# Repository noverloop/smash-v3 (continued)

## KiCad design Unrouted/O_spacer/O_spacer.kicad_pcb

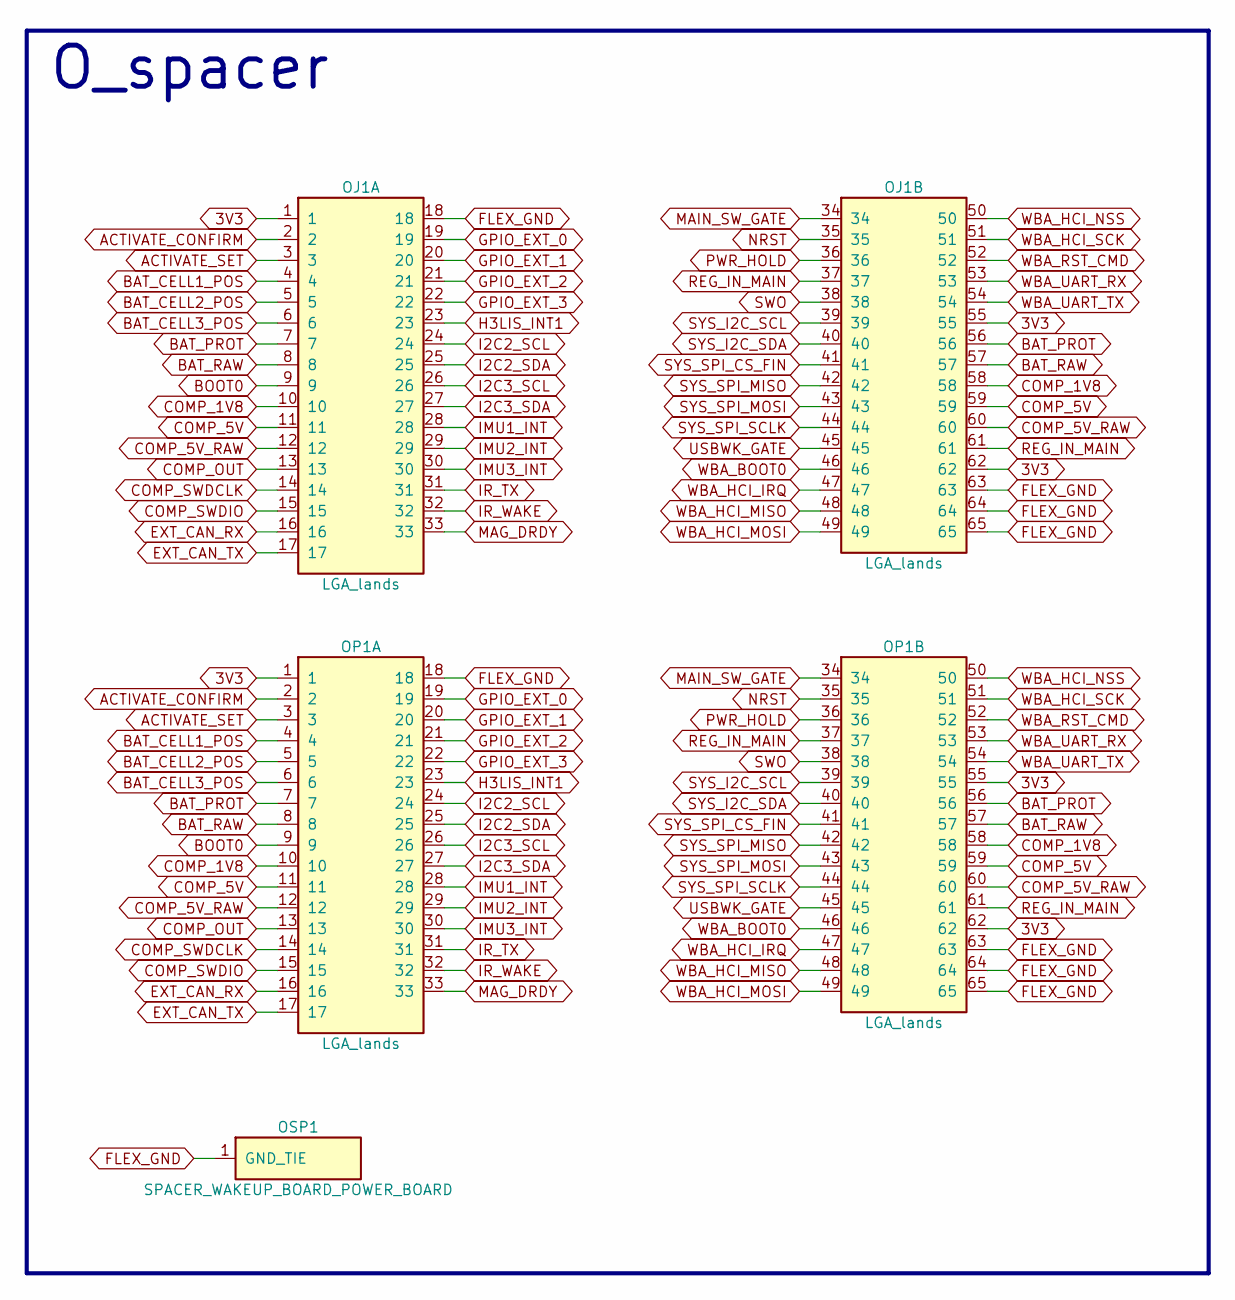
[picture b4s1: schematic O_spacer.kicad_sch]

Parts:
OJ1: LGA_lands; J_spacer_wakeup_board_power_board_top; MPN LGA_lands
OP1: LGA_lands; P_spacer_wakeup_board_power_board_bot; MPN LGA_lands
OSP1: SPACER_WAKEUP_BOARD_POWER_BOARD; Spacer_Mechanical_34mm

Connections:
3V3: OJ1.1, OJ1.55, OJ1.62, OP1.1, OP1.55, OP1.62
ACTIVATE_CONFIRM: OJ1.2, OP1.2
ACTIVATE_SET: OJ1.3, OP1.3
BAT_CELL1_POS: OJ1.4, OP1.4
BAT_CELL2_POS: OJ1.5, OP1.5
BAT_CELL3_POS: OJ1.6, OP1.6
BAT_PROT: OJ1.7, OJ1.56, OP1.7, OP1.56
BAT_RAW: OJ1.8, OJ1.57, OP1.8, OP1.57
BOOT0: OJ1.9, OP1.9
COMP_1V8: OJ1.10, OJ1.58, OP1.10, OP1.58
COMP_5V: OJ1.11, OJ1.59, OP1.11, OP1.59
COMP_5V_RAW: OJ1.12, OJ1.60, OP1.12, OP1.60
COMP_OUT: OJ1.13, OP1.13
COMP_SWDCLK: OJ1.14, OP1.14
COMP_SWDIO: OJ1.15, OP1.15
EXT_CAN_RX: OJ1.16, OP1.16
EXT_CAN_TX: OJ1.17, OP1.17
FLEX_GND: OJ1.18, OJ1.63, OJ1.64, OJ1.65, OP1.18, OP1.63, OP1.64, OP1.65, OSP1.1
GPIO_EXT_0: OJ1.19, OP1.19
GPIO_EXT_1: OJ1.20, OP1.20
GPIO_EXT_2: OJ1.21, OP1.21
GPIO_EXT_3: OJ1.22, OP1.22
H3LIS_INT1: OJ1.23, OP1.23
I2C2_SCL: OJ1.24, OP1.24
I2C2_SDA: OJ1.25, OP1.25
I2C3_SCL: OJ1.26, OP1.26
I2C3_SDA: OJ1.27, OP1.27
IMU1_INT: OJ1.28, OP1.28
IMU2_INT: OJ1.29, OP1.29
IMU3_INT: OJ1.30, OP1.30
IR_TX: OJ1.31, OP1.31
IR_WAKE: OJ1.32, OP1.32
MAG_DRDY: OJ1.33, OP1.33
MAIN_SW_GATE: OJ1.34, OP1.34
NRST: OJ1.35, OP1.35
PWR_HOLD: OJ1.36, OP1.36
REG_IN_MAIN: OJ1.37, OJ1.61, OP1.37, OP1.61
SWO: OJ1.38, OP1.38
SYS_I2C_SCL: OJ1.39, OP1.39
SYS_I2C_SDA: OJ1.40, OP1.40
SYS_SPI_CS_FIN: OJ1.41, OP1.41
SYS_SPI_MISO: OJ1.42, OP1.42
SYS_SPI_MOSI: OJ1.43, OP1.43
SYS_SPI_SCLK: OJ1.44, OP1.44
USBWK_GATE: OJ1.45, OP1.45
WBA_BOOT0: OJ1.46, OP1.46
WBA_HCI_IRQ: OJ1.47, OP1.47
WBA_HCI_MISO: OJ1.48, OP1.48
WBA_HCI_MOSI: OJ1.49, OP1.49
WBA_HCI_NSS: OJ1.50, OP1.50
WBA_HCI_SCK: OJ1.51, OP1.51
WBA_RST_CMD: OJ1.52, OP1.52
WBA_UART_RX: OJ1.53, OP1.53
WBA_UART_TX: OJ1.54, OP1.54

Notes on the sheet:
O_spacer

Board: 2 copper layers, 5 parts (1 on the bottom side), 54 nets, no tracks yet.

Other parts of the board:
OMH1, OMH2: smash_mech_potting

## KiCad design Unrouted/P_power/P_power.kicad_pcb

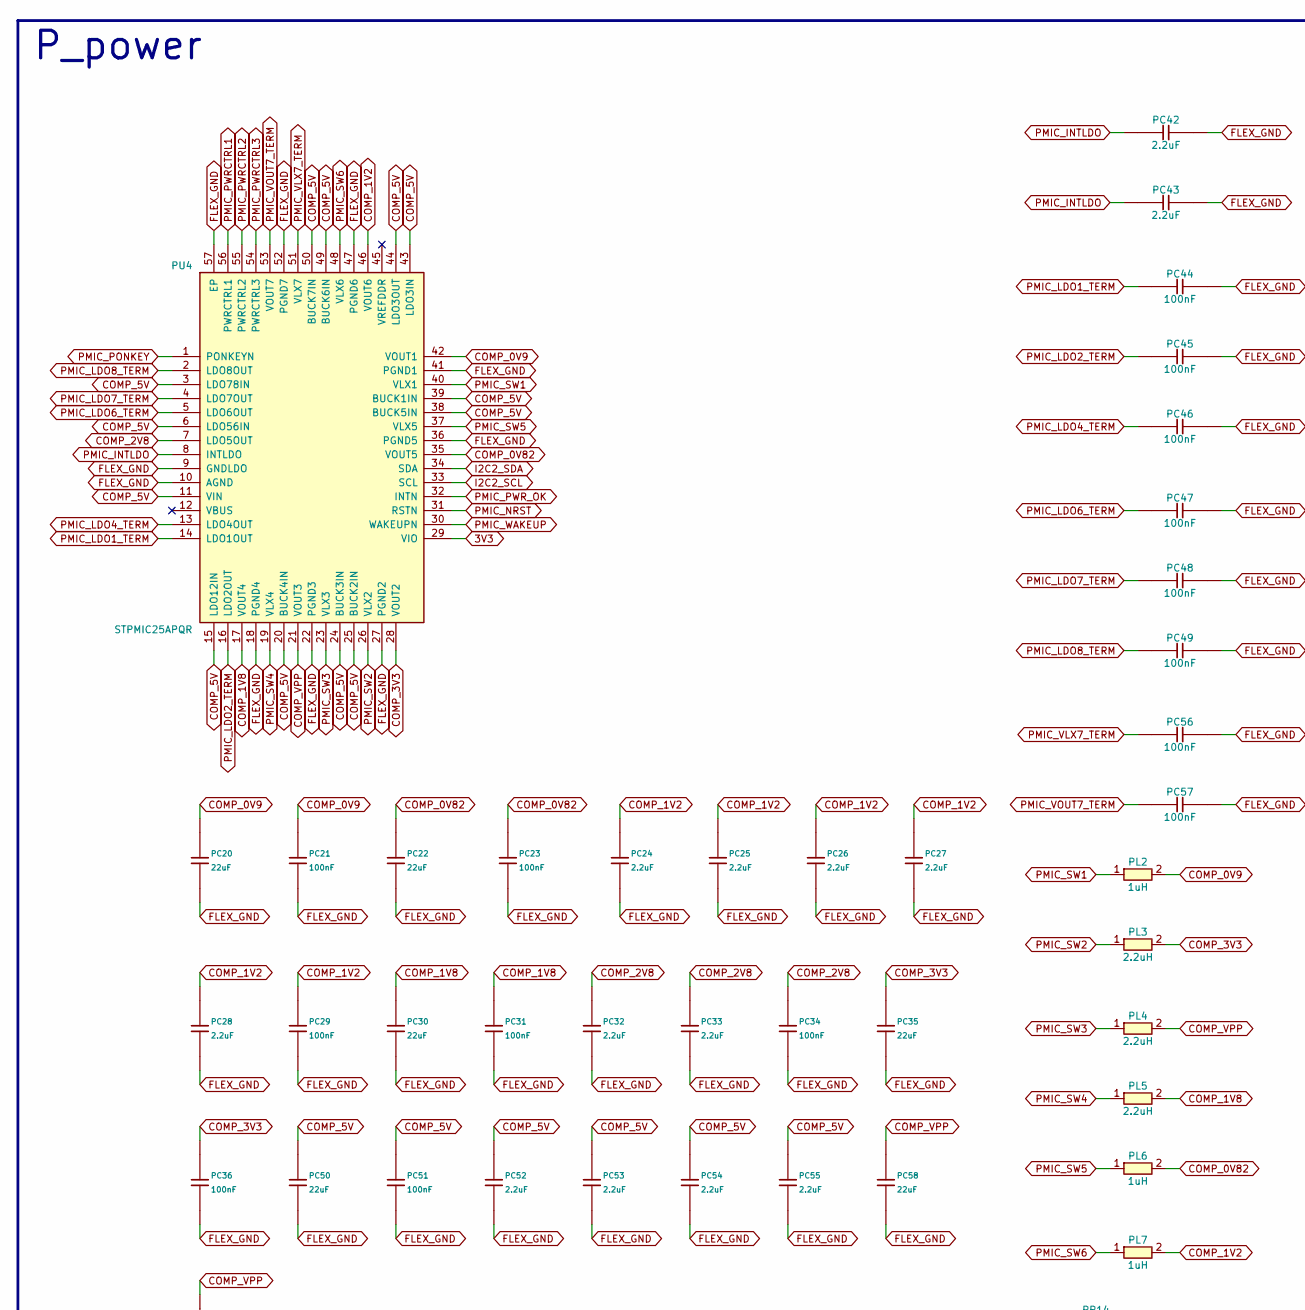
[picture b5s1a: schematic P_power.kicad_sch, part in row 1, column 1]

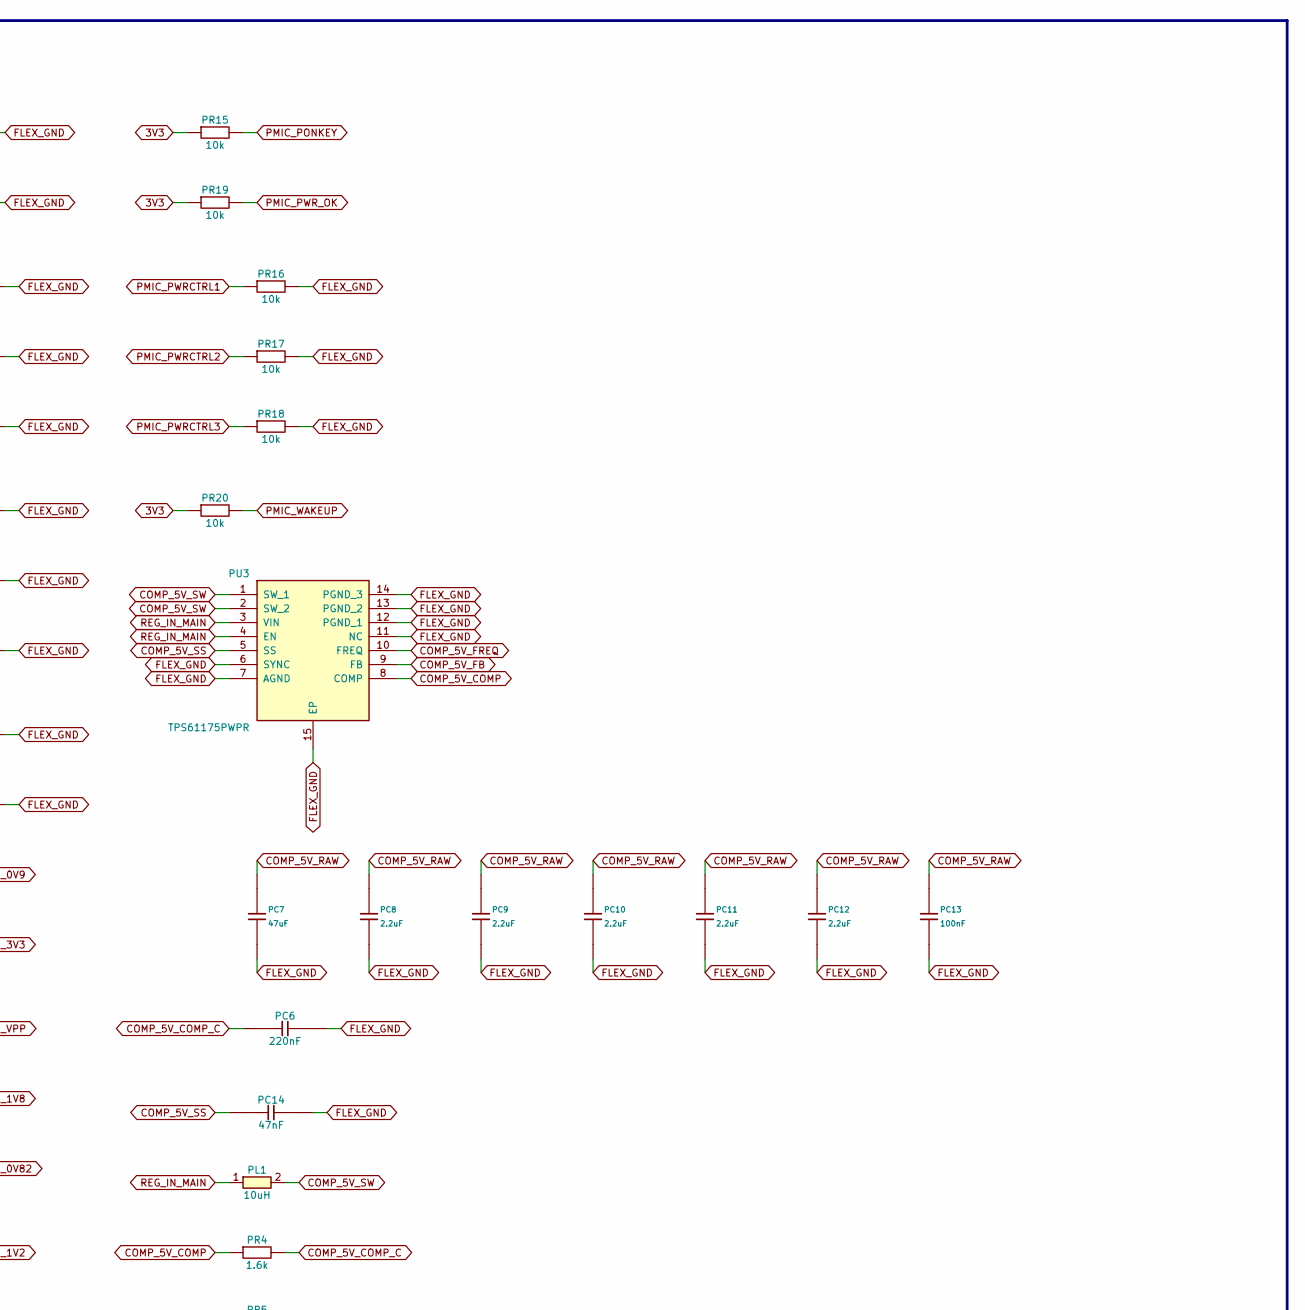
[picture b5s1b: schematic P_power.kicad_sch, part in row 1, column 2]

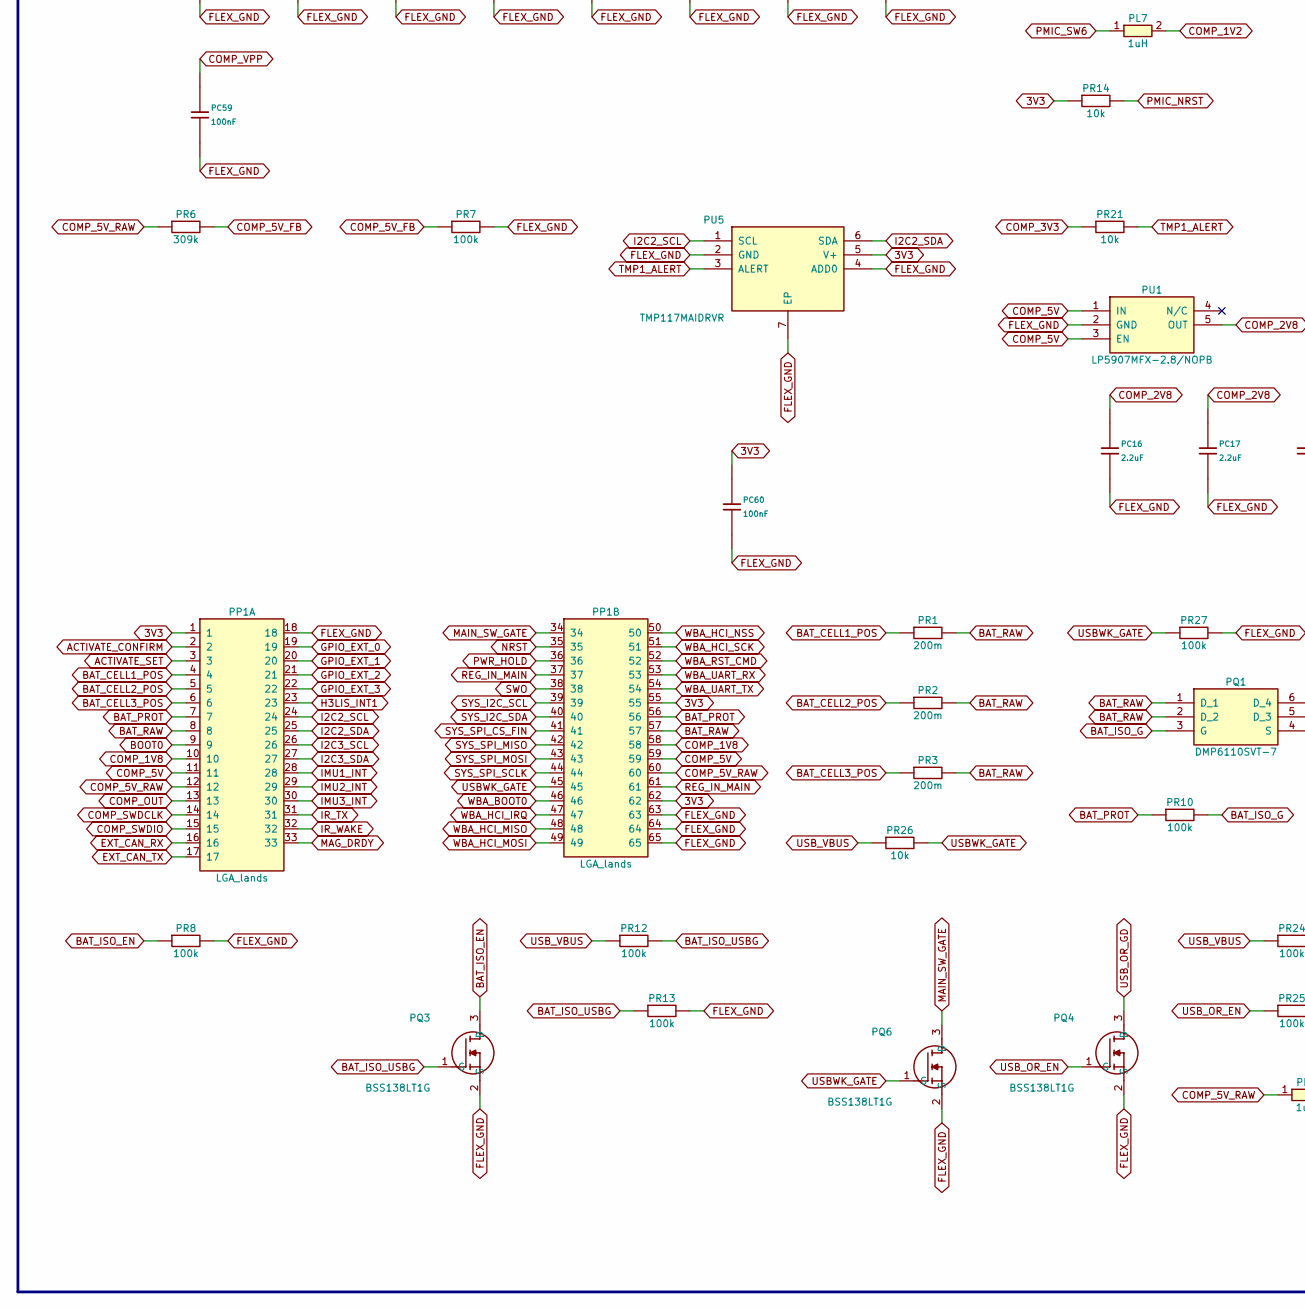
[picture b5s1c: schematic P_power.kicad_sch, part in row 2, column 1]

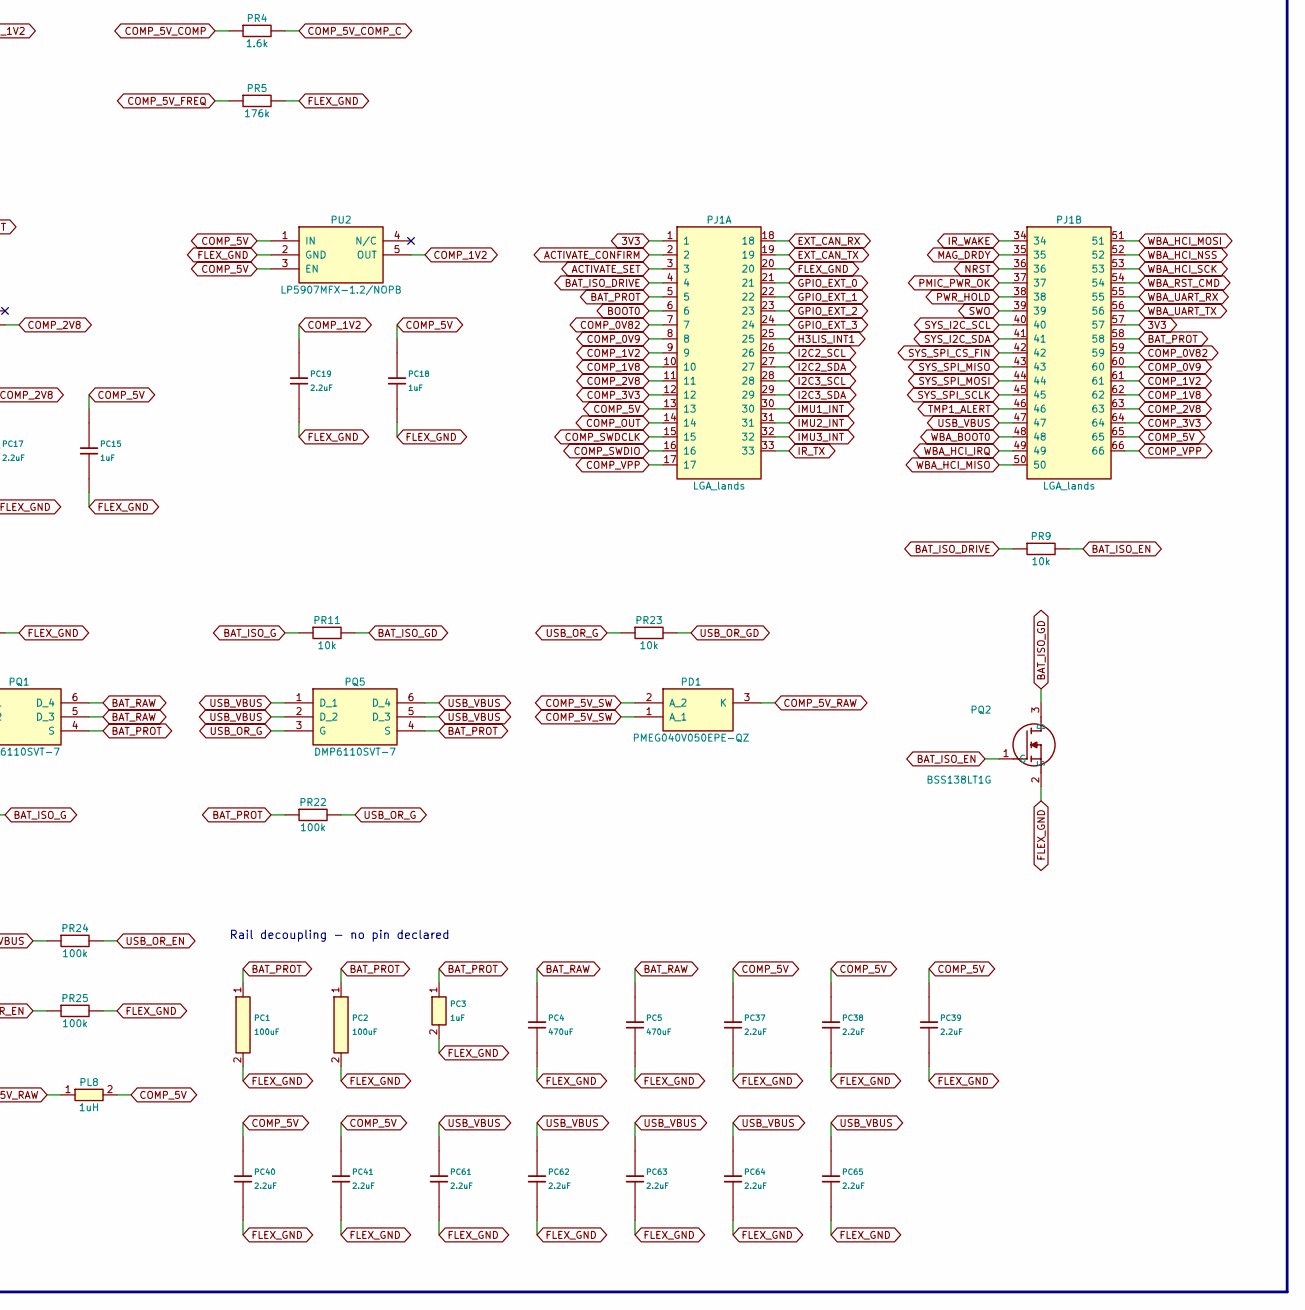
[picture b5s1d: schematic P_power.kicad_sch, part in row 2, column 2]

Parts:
PC1, PC2: 100uF; Capacitor_Tantalum_SMD_CP_EIA-7343-15_Kemet-W; MPN T528W 100uF (7343-15 thinnest variant)
PC3, PC15, PC18: 1uF; Capacitor_SMD_C_0805_2012Metric; MPN C-Series MIL-PRF-32535 X7R 0805 1uF
PC4, PC5: 470uF; Capacitor_Tantalum_SMD_CP_EIA-7343-15_Kemet-W; MPN T528W 470uF (7343-15 thinnest variant)
PC6: 220nF; Capacitor_SMD_C_0603_1608Metric; MPN C-Series MIL-PRF-32535 X7R 0603 220nF
PC7: 47uF; Capacitor_Tantalum_SMD_CP_EIA-7343-15_Kemet-W; MPN T528W 47uF (7343-15 thinnest variant)
PC8, PC9, PC10, PC11, PC12, PC16, PC17, PC19, PC24, PC25, PC26, PC27, PC28, PC32, PC33, PC37, PC38, PC39, PC40, PC41, PC42, PC43, PC52, PC53, PC54, PC55, PC61, PC62, PC63, PC64, PC65: 2.2uF; Capacitor_SMD_C_0603_1608Metric; MPN C-Series MIL-PRF-32535 X7R 0603 2.2uF
PC13, PC21, PC23, PC29, PC31, PC34, PC36, PC44, PC45, PC46, PC47, PC48, PC49, PC51, PC56, PC57, PC59, PC60: 100nF; Capacitor_SMD_C_0402_1005Metric; MPN C0402 X7R 100nF
PC14: 47nF; Capacitor_SMD_C_0402_1005Metric; MPN C0402 X7R 47nF
PC20, PC22, PC30, PC35, PC50, PC58: 22uF; Capacitor_Tantalum_SMD_CP_EIA-3528-12_Kemet-T; MPN T491T 22uF (3528-12 thinnest variant)
PD1: PMEG040V050EPE-QZ; PMEG040V050EPEQZ; MPN PMEG040V050EPE-QZ
PJ1: LGA_lands; J_power_board_spacer_power_board_companion_compute; MPN LGA_lands
PL1: 10uH; INDPM4848X280N; MPN 744043100
PL2, PL6, PL7, PL8: 1uH; Inductor_SMD_L_2012_2.0x1.25mm; MPN TMS201210ALM-1R0MTAA
PL3, PL4, PL5: 2.2uH; Inductor_SMD_L_2012_2.0x1.25mm; MPN TMS201210ALM-2R2MTAA
PP1: LGA_lands; P_power_board_spacer_wakeup_board_power_board; MPN LGA_lands
PQ1, PQ5: DMP6110SVT-7; SOT95P280X100-6N; MPN DMP6110SVT-7
PQ2, PQ3, PQ4, PQ6: BSS138LT1G; SOT96P237X111-3N; MPN BSS138LT1G
PR1, PR2, PR3: 200m; Resistor_SMD_R_0402_1005Metric; MPN CRCW0402 200m 1% e3
PR4: 1.6k; Resistor_SMD_R_0402_1005Metric; MPN CRCW0402 1.6k 1% e3
PR5: 176k; Resistor_SMD_R_0402_1005Metric; MPN CRCW0402 176k 1% e3
PR6: 309k; Resistor_SMD_R_0402_1005Metric; MPN CRCW0402 309k 1% e3
PR7, PR8, PR10, PR12, PR13, PR22, PR24, PR25, PR27: 100k; Resistor_SMD_R_0402_1005Metric; MPN CRCW0402 100k 1% e3
PR9, PR11, PR14, PR15, PR16, PR17, PR18, PR19, PR20, PR21, PR23, PR26: 10k; Resistor_SMD_R_0402_1005Metric; MPN CRCW0402 10k 1% e3
PU1: LP5907MFX-2.8/NOPB; SOT95P280X145-5N; MPN LP5907MFX-2.8/NOPB
PU2: LP5907MFX-1.2/NOPB; SOT95P280X145-5N; MPN LP5907MFX-1.2/NOPB
PU3: TPS61175PWPR; SOP65P640X120-15N; MPN TPS61175PWPR
PU4: STPMIC25APQR; QFN40P650X650X90-57N-D; MPN STPMIC25APQR
PU5: TMP117MAIDRVR; SON65P200X200X80-7N; MPN TMP117MAIDRVR

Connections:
3V3: PC60.1 (+), PJ1.1, PJ1.57, PP1.1, PP1.55, PP1.62, PR14.1, PR15.1, PR19.1, PR20.1, PU4.29 (VIO), PU5.5 (V+)
ACTIVATE_CONFIRM: PJ1.2, PP1.2
ACTIVATE_SET: PJ1.3, PP1.3
BAT_CELL1_POS: PP1.4, PR1.1
BAT_CELL2_POS: PP1.5, PR2.1
BAT_CELL3_POS: PP1.6, PR3.1
BAT_ISO_DRIVE: PJ1.4, PR9.1
BAT_ISO_EN: PQ2.1 (G), PQ3.3 (D), PR8.1, PR9.2
BAT_ISO_G: PQ1.3 (G), PR10.2, PR11.1
BAT_ISO_GD: PQ2.3 (D), PR11.2
BAT_ISO_USBG: PQ3.1 (G), PR12.2, PR13.1
BAT_PROT: PC1.1 (+), PC2.1 (+), PC3.1, PJ1.5, PJ1.58, PP1.7, PP1.56, PQ1.4 (S), PQ5.4 (S), PR10.1, PR22.1
BAT_RAW: PC4.1 (+), PC5.1 (+), PP1.8, PP1.57, PQ1.1 (D_1), PQ1.2 (D_2), PQ1.5 (D_3), PQ1.6 (D_4), PR1.2, PR2.2, PR3.2
BOOT0: PJ1.6, PP1.9
COMP_0V9: PC20.1 (+), PC21.1 (+), PJ1.8, PJ1.60, PL2.2, PU4.42 (VOUT1)
COMP_0V82: PC22.1 (+), PC23.1 (+), PJ1.7, PJ1.59, PL6.2, PU4.35 (VOUT5)
COMP_1V2: PC19.1 (+), PC24.1 (+), PC25.1 (+), PC26.1 (+), PC27.1 (+), PC28.1 (+), PC29.1 (+), PJ1.9, PJ1.61, PL7.2, PU2.5 (OUT), PU4.46 (VOUT6)
COMP_1V8: PC30.1 (+), PC31.1 (+), PJ1.10, PJ1.62, PL5.2, PP1.10, PP1.58, PU4.17 (VOUT4)
COMP_2V8: PC16.1 (+), PC17.1 (+), PC32.1 (+), PC33.1 (+), PC34.1 (+), PJ1.11, PJ1.63, PU1.5 (OUT), PU4.7 (LDO5OUT)
COMP_3V3: PC35.1 (+), PC36.1 (+), PJ1.12, PJ1.64, PL3.2, PR21.1, PU4.28 (VOUT2)
COMP_5V: PC15.1 (+), PC18.1 (+), PC37.1 (+), PC38.1 (+), PC39.1 (+), PC40.1 (+), PC41.1 (+), PC50.1 (+), PC51.1 (+), PC52.1 (+), PC53.1 (+), PC54.1 (+), PC55.1 (+), PJ1.13, PJ1.65, PL8.2, PP1.11, PP1.59, PU1.1 (IN), PU1.3 (EN), PU2.1 (IN), PU2.3 (EN), PU4.3 (LDO78IN), PU4.6 (LDO56IN), PU4.11 (VIN), PU4.15 (LDO12IN), PU4.20 (BUCK4IN), PU4.24 (BUCK3IN), PU4.25 (BUCK2IN), PU4.38 (BUCK5IN), PU4.39 (BUCK1IN), PU4.43 (LDO3IN), PU4.44 (LDO3OUT), PU4.49 (BUCK6IN), PU4.50 (BUCK7IN)
COMP_5V_COMP: PR4.1, PU3.8 (COMP)
COMP_5V_COMP_C: PC6.1 (+), PR4.2
COMP_5V_FB: PR6.2, PR7.1, PU3.9 (FB)
COMP_5V_FREQ: PR5.1, PU3.10 (FREQ)
COMP_5V_RAW: PC7.1 (+), PC8.1 (+), PC9.1 (+), PC10.1 (+), PC11.1 (+), PC12.1 (+), PC13.1 (+), PD1.3 (K), PL8.1, PP1.12, PP1.60, PR6.1
COMP_5V_SS: PC14.1 (+), PU3.5 (SS)
COMP_5V_SW: PD1.1 (A_1), PD1.2 (A_2), PL1.2, PU3.1 (SW_1), PU3.2 (SW_2)
COMP_OUT: PJ1.14, PP1.13
COMP_SWDCLK: PJ1.15, PP1.14
COMP_SWDIO: PJ1.16, PP1.15
COMP_VPP: PC58.1 (+), PC59.1 (+), PJ1.17, PJ1.66, PL4.2, PU4.21 (VOUT3)
EXT_CAN_RX: PJ1.18, PP1.16
EXT_CAN_TX: PJ1.19, PP1.17
FLEX_GND: PC1.2 (-), PC2.2 (-), PC3.2, PC4.2 (-), PC5.2 (-), PC6.2 (-), PC7.2 (-), PC8.2 (-), PC9.2 (-), PC10.2 (-), PC11.2 (-), PC12.2 (-), PC13.2 (-), PC14.2 (-), PC15.2 (-), PC16.2 (-), PC17.2 (-), PC18.2 (-), PC19.2 (-), PC20.2 (-), PC21.2 (-), PC22.2 (-), PC23.2 (-), PC24.2 (-), PC25.2 (-), PC26.2 (-), PC27.2 (-), PC28.2 (-), PC29.2 (-), PC30.2 (-), PC31.2 (-), PC32.2 (-), PC33.2 (-), PC34.2 (-), PC35.2 (-), PC36.2 (-), PC37.2 (-), PC38.2 (-), PC39.2 (-), PC40.2 (-), PC41.2 (-), PC42.2 (-), PC43.2 (-), PC44.2 (-), PC45.2 (-), PC46.2 (-), PC47.2 (-), PC48.2 (-), PC49.2 (-), PC50.2 (-), PC51.2 (-), PC52.2 (-), PC53.2 (-), PC54.2 (-), PC55.2 (-), PC56.2 (-), PC57.2 (-), PC58.2 (-), PC59.2 (-), PC60.2 (-), PC61.2 (-), PC62.2 (-), PC63.2 (-), PC64.2 (-), PC65.2 (-), PJ1.20, PP1.18, PP1.63, PP1.64, PP1.65, PQ2.2 (S), PQ3.2 (S), PQ4.2 (S), PQ6.2 (S), PR5.2, PR7.2, PR8.2, PR13.2, PR16.2, PR17.2, PR18.2, PR25.2, PR27.2, PU1.2 (GND), PU2.2 (GND), PU3.6 (SYNC), PU3.7 (AGND), PU3.11 (NC), PU3.12 (PGND_1), PU3.13 (PGND_2), PU3.14 (PGND_3), PU3.15 (EP), PU4.9 (GNDLDO), PU4.10 (AGND), PU4.18 (PGND4), PU4.22 (PGND3), PU4.27 (PGND2), PU4.36 (PGND5), PU4.41 (PGND1), PU4.47 (PGND6), PU4.52 (PGND7), PU4.57 (EP), PU5.2 (GND), PU5.4 (ADD0), PU5.7 (EP)
GPIO_EXT_0: PJ1.21, PP1.19
GPIO_EXT_1: PJ1.22, PP1.20
GPIO_EXT_2: PJ1.23, PP1.21
GPIO_EXT_3: PJ1.24, PP1.22
H3LIS_INT1: PJ1.25, PP1.23
I2C2_SCL: PJ1.26, PP1.24, PU4.33 (SCL), PU5.1 (SCL)
I2C2_SDA: PJ1.27, PP1.25, PU4.34 (SDA), PU5.6 (SDA)
I2C3_SCL: PJ1.28, PP1.26
I2C3_SDA: PJ1.29, PP1.27
IMU1_INT: PJ1.30, PP1.28
IMU2_INT: PJ1.31, PP1.29
IMU3_INT: PJ1.32, PP1.30
IR_TX: PJ1.33, PP1.31
IR_WAKE: PJ1.34, PP1.32
MAG_DRDY: PJ1.35, PP1.33
MAIN_SW_GATE: PP1.34, PQ6.3 (D)
NRST: PJ1.36, PP1.35
PMIC_INTLDO: PC42.1 (+), PC43.1 (+), PU4.8 (INTLDO)
PMIC_LDO1_TERM: PC44.1 (+), PU4.14 (LDO1OUT)
PMIC_LDO2_TERM: PC45.1 (+), PU4.16 (LDO2OUT)
PMIC_LDO4_TERM: PC46.1 (+), PU4.13 (LDO4OUT)
PMIC_LDO6_TERM: PC47.1 (+), PU4.5 (LDO6OUT)
PMIC_LDO7_TERM: PC48.1 (+), PU4.4 (LDO7OUT)
PMIC_LDO8_TERM: PC49.1 (+), PU4.2 (LDO8OUT)
PMIC_NRST: PR14.2, PU4.31 (RSTN)
PMIC_PONKEY: PR15.2, PU4.1 (PONKEYN)
PMIC_PWRCTRL1: PR16.1, PU4.56 (PWRCTRL1)
PMIC_PWRCTRL2: PR17.1, PU4.55 (PWRCTRL2)
PMIC_PWRCTRL3: PR18.1, PU4.54 (PWRCTRL3)
PMIC_PWR_OK: PJ1.37, PR19.2, PU4.32 (INTN)
PMIC_SW1: PL2.1, PU4.40 (VLX1)
PMIC_SW2: PL3.1, PU4.26 (VLX2)
PMIC_SW3: PL4.1, PU4.23 (VLX3)
PMIC_SW4: PL5.1, PU4.19 (VLX4)
PMIC_SW5: PL6.1, PU4.37 (VLX5)
PMIC_SW6: PL7.1, PU4.48 (VLX6)
PMIC_VLX7_TERM: PC56.1 (+), PU4.51 (VLX7)
PMIC_VOUT7_TERM: PC57.1 (+), PU4.53 (VOUT7)
PMIC_WAKEUP: PR20.2, PU4.30 (WAKEUPN)
PWR_HOLD: PJ1.38, PP1.36
REG_IN_MAIN: PL1.1, PP1.37, PP1.61, PU3.3 (VIN), PU3.4 (EN)
SWO: PJ1.39, PP1.38
SYS_I2C_SCL: PJ1.40, PP1.39
SYS_I2C_SDA: PJ1.41, PP1.40
SYS_SPI_CS_FIN: PJ1.42, PP1.41
SYS_SPI_MISO: PJ1.43, PP1.42
SYS_SPI_MOSI: PJ1.44, PP1.43
SYS_SPI_SCLK: PJ1.45, PP1.44
TMP1_ALERT: PJ1.46, PR21.2, PU5.3 (ALERT)
USBWK_GATE: PP1.45, PQ6.1 (G), PR26.2, PR27.1
USB_OR_EN: PQ4.1 (G), PR24.2, PR25.1
USB_OR_G: PQ5.3 (G), PR22.2, PR23.1
USB_OR_GD: PQ4.3 (D), PR23.2
USB_VBUS: PC61.1 (+), PC62.1 (+), PC63.1 (+), PC64.1 (+), PC65.1 (+), PJ1.47, PQ5.1 (D_1), PQ5.2 (D_2), PQ5.5 (D_3), PQ5.6 (D_4), PR12.1, PR24.1, PR26.1
WBA_BOOT0: PJ1.48, PP1.46
WBA_HCI_IRQ: PJ1.49, PP1.47
WBA_HCI_MISO: PJ1.50, PP1.48
WBA_HCI_MOSI: PJ1.51, PP1.49
WBA_HCI_NSS: PJ1.52, PP1.50
WBA_HCI_SCK: PJ1.53, PP1.51
WBA_RST_CMD: PJ1.54, PP1.52
WBA_UART_RX: PJ1.55, PP1.53
WBA_UART_TX: PJ1.56, PP1.54

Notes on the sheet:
P_power
Rail decoupling - no pin declared

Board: 14 copper layers, 116 parts (45 on the bottom side), 98 nets, no tracks yet.

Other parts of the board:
PMH1, PMH2: smash_mech_potting
